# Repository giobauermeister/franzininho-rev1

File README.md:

# Franzininho

Essa é a versão KiCAD da placa Franzininho desenvolvida por Fábio Souza

Uma placa Arduino facil de montar. Possui placa de circuito impresso em face simples e componentes pth. 

Essa placa foi desenvolvida para as atividades no FAB LAB Livre SP durante o Arduino Day 2017 em São Paulo: http://arduinosaopaulo.cc

Você pode facilmente fazer a sua usando uma CNC ou até mesmo métodos caseiros.

É importante usar uma placa de circuito impresso de 2.4 mm para um boo conexão na USB.

# Caracteríticas:

Microcontrolador ATtiny85 DIP, Conector USB na placa, 5 Pinos de I/O, LED de uso geral, LED de POWER

Artigo no Embarcados: https://www.embarcados.com.br/franzininho-um-arduino-para-todos/

# Programação

Para programação na IDE arduino, deve ser gravado o bootloader, conforme exmplicado no post do Mauricio Jabur no Fazedores: http://blog.fazedores.com/attiny85-com-v-usb-como-gravar-o-bootloader-usando-arduino/

# Material para oficinas

Em constução

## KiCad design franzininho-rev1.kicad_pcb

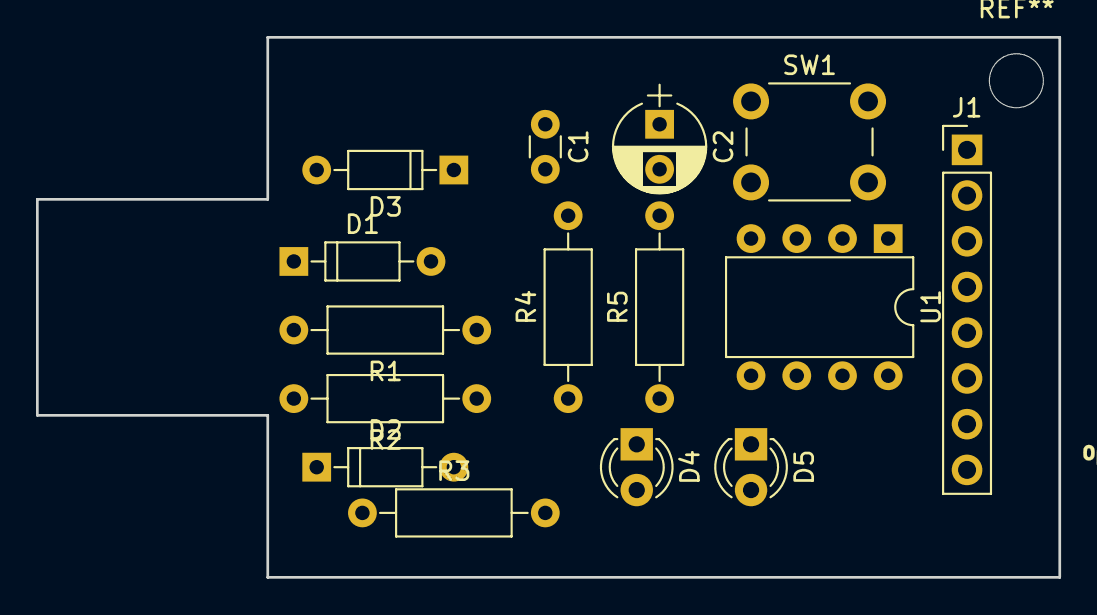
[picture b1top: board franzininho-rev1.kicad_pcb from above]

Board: 2 copper layers, 56.8 x 30.0 mm, 17 parts (1 on the bottom side), 13 nets, no tracks yet.

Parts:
C1: 0.1uF; C_Disc_D3.0mm_W1.6mm_P2.50mm
C2: 10uF; CP_Radial_D5.0mm_P2.50mm
D1, D2: BZT52; D_DO-35_SOD27_P7.62mm_Horizontal
D3: 1N4148; D_DO-35_SOD27_P7.62mm_Horizontal
D4: LED_ON; LED_D3.0mm
D5: LED; LED_D3.0mm
J1: CONN_01X08; Pin_Header_Straight_1x08_Pitch2.54mm
LOGO1: open hardware; OSHW-Logo2_9.8x8mm_SilkScreen
R1, R2: 68R; R_Axial_DIN0207_L6.3mm_D2.5mm_P10.16mm_Horizontal
R3: 1K5; R_Axial_DIN0207_L6.3mm_D2.5mm_P10.16mm_Horizontal
R4, R5: 1K; R_Axial_DIN0207_L6.3mm_D2.5mm_P10.16mm_Horizontal
SW1: SW_RESET; SW_PUSH_6mm
U1: ATTINY85-20PU; DIP-8_W7.62mm
U2: USB_conn; USB_COPPER

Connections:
+5V: C1.1, C2.1, D3.1, D4.2, J1.7, R3.1, U1.8
GND: C1.2, C2.2, D1.2, D2.2, J1.8, R4.2, R5.1, SW1.2, U1.4, U2.4
unnamed: D1.1, R1.2, R3.2, U2.2
unnamed: D2.1, R2.2, U2.3
unnamed: D3.2, U2.1
unnamed: D4.1, R4.1
unnamed: D5.1, R5.2
unnamed: D5.2, J1.2, U1.6
unnamed: J1.1, U1.5
unnamed: J1.3, U1.7
unnamed: J1.4, R1.1, U1.2
unnamed: J1.5, SW1.1, U1.1
unnamed: J1.6, R2.1, U1.3

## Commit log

2017-07-09 add board layout
